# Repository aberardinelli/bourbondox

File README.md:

# bourbondox

`pcb/rev1` folder contains the KiCAD pcb files for v0.1 (received 2021-07-02)

`pcb/rev2` folder contains the KiCAD pcb files for v0.2 (received 2021-07-06)

`pcb/rev3` folder contains the KiCAD pcb files for v0.3 (received 2021-07-19)

`pcb/rev4` folder contains the KiCAD pcb files for v0.4 (received 2021-07-29)

`pcb/rev5` folder contains the KiCAD pcb files for v1.0 (received 2021-08-13)

`firmware` folder contains the qmk firmware files

`case/v1` folder contains the FreeCAD and dxf files for a stacked acrylic case that aligns with the v1.0 pcb (finished 2021-09-10)

There is also a json file (`keyboard-layout_rev1.0.json`) which could be used on keyboard-layout-editor.com

## Changelog and documentation of issues

### v0.1

* Only had one side printed. Diodes were mistakenly put on the front of the PCB in my schematic when they should be on the back.
* Soldered on reset button, promicro controller, and diodes.
* Tested each switch with tweezers. 
* All switches in columns 0, 1, 2, 3, and 4 worked as expected.
* All switches in columns 5 and 6 failed to register. Reset button failed to work.

### v0.2

* Had both sides printed this time. Completely redid the routing from scratch because I wasn't happy with the first version. Did all this and ordered the v0.2 prototypes before I had even received and tested v0.1.
* Soldered reset buttons, TRRS jacks, OLED screens, promicro controllers, diodes, and switches on both halves. Soldered resistors on right side only.
* Reset buttons still didn't work.  But... On each side, when plugged in alone (not connected to other half): All switches worked as expected. Both OLED screens worked as expected.
* When the sides are connected via TRRS cable, switches and OLED screens stopped working. This led me to believe there was a problem with the routing with the TRRS jacks. I ruled out a problem with the cable since I tried two different TRRS cables, both of which worked fine with two other split keyboards.
* Stagger on left hand felt extremely comfortable but right hand was unnatural.

### v0.3

* Changed the footprints on the PCB for the TRRS jacks and reset switches. Rerouted those components on the schematic.
* Reduced the stagger by a small bit on the left side. Reduced the stagger by a lot on the right side.
* Reset buttons work now, on both halves. 
* When it comes to testing the TRRS connection, there are multiple outcomes depending on configuration:
    * If right half has Elite-C and it is connected via USB-C cable to the computer, no switches register and OLEDs are blank.
    * If left half has ProMicro and it is connected via micro USB cable to the computer, no switches register, but the OLEDs each show the same garbled output (first few letters are clear and correct but the rest is nonsense).
    * If NOT connected via TRRS, but each half is connected via its respective USB cable directly to the computer, then OLED screens work as expected and all switches register as expected with tweezers.
* Stagger on left hand seems perfect; right hand might still need adjustments on pinky but seems perfect now for middle and ring fingers. 

### v0.4

* Changed the split communication to serial to allow OLED screens to use i2c. This required changing the routing and footprints in the schematics for the TRRS jacks.
* Very minor adjustments made to spacing of holes for OLED covers.
* Thumb cluster on right side was not great for my use case; rotated the keys on that side. 
* Increased the spacebar size on left side to 2u for more likely compatibility with keycap kits.

## v1.0 photos

*Initial build of v1.0 with cheap tenting provided by acrylic photo frames*

*v1.0 with better tenting provided by magnetic cell phone holders*

## v0.4 photo

*First fully functional build!*

## v0.3 photos

*Not plugged in*

*Halves are NOT connected, each half is connected to computer via its own cable. OLEDs, switches, and reset buttons work as expected*

*TRRS connecting the halves, connected to computer via USB-C cable plugged into Elite-C controller on right half of keyboard (controller power buttons light up, but no OLEDs and no switches register)*

*TRRS connecting the halves, connected to computer via micro USB cable plugged into ProMicro controller on left half of keyboard (controller power buttons light up, but no switches register; OLEDs light up but output is garbled)*

## v0.2 photo

*Everything's soldered, but it's not plugged in*

## v0.1 photos

*No soldering done yet, just placing switches and keycaps to verify fit.*

*Soldered diodes, promicro, and reset button to the front. Yes, I know the diodes are supposed to be on the back of the PCB. This is fixed for v0.2.*

*View of the soldering for the promicro on the back of the PCB.*

*Promicro is flashed and soldered. Ready for testing!*

# Acknowledgements

Thank you to ai03 and masterzen for your extensive keyboard pcb design tutorials posted online as resources for the community.

Thank you to the designers of the redox, lily58, and corne-cherry for sharing your work as open source. These were inspirational and helpful resources during my design of this keyboard.

Special thanks to the Keycraft Collective discord community, especially users astra and matthewdias, for their encouragement, feedback, input, and troubleshooting.

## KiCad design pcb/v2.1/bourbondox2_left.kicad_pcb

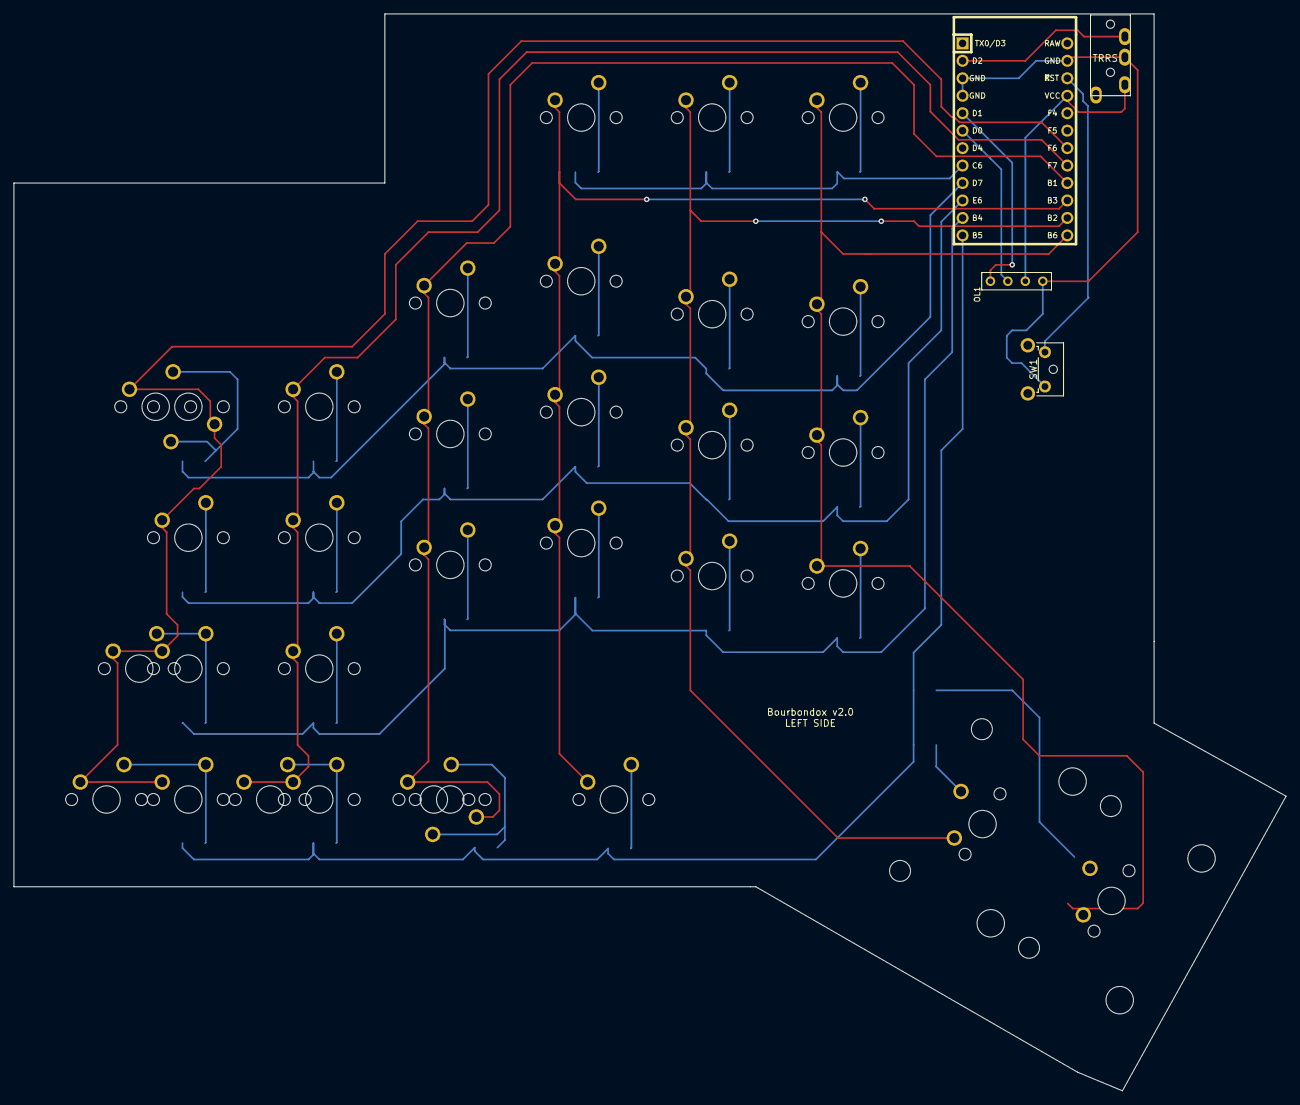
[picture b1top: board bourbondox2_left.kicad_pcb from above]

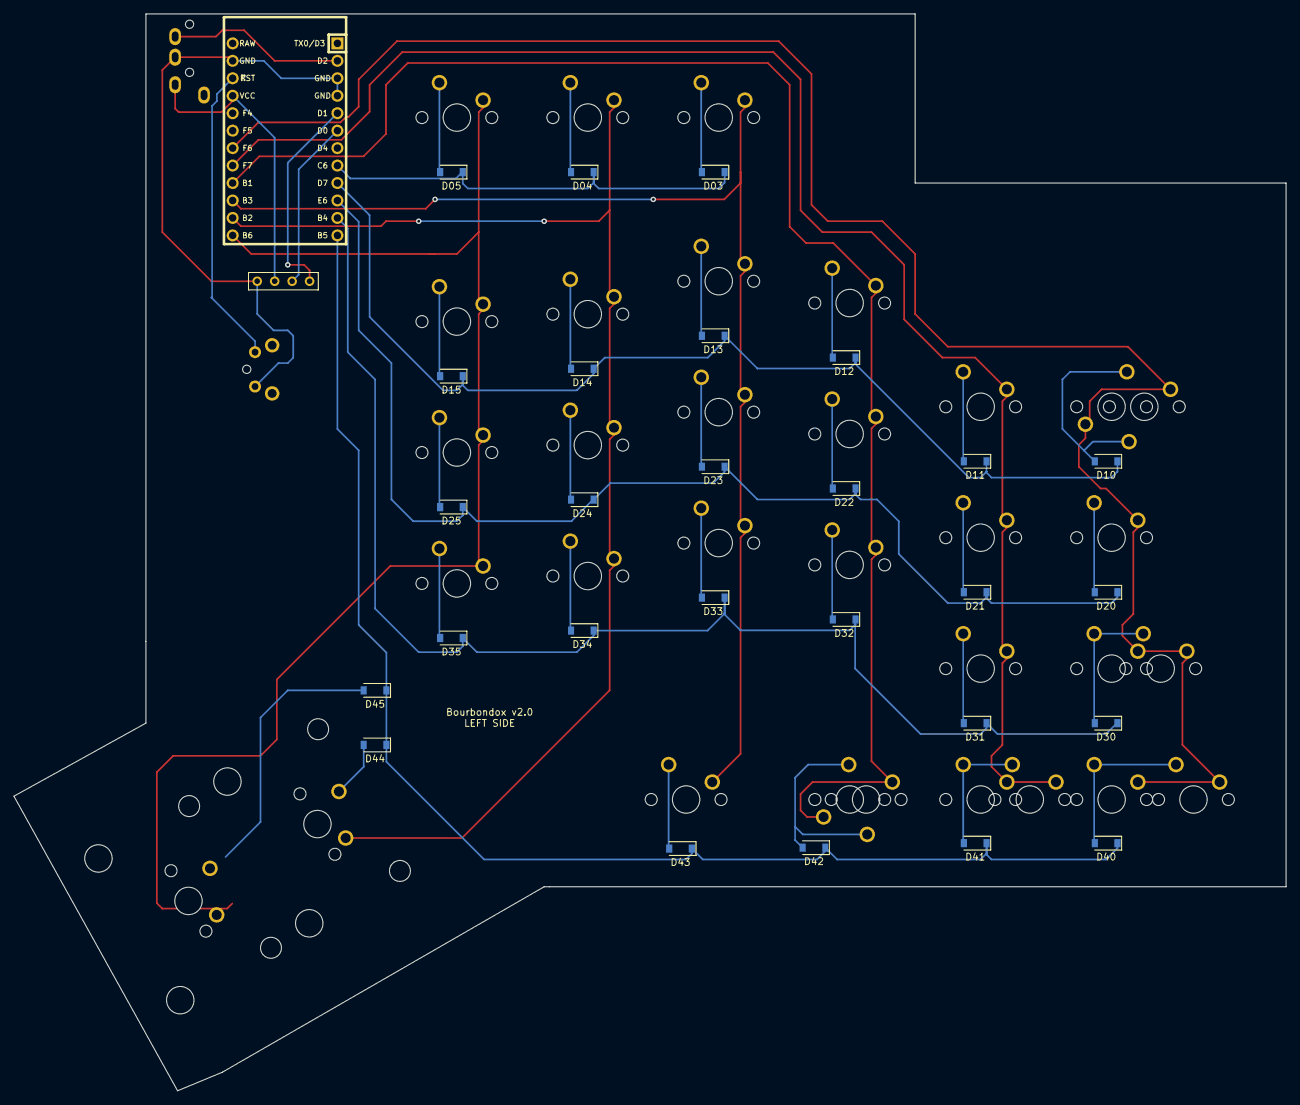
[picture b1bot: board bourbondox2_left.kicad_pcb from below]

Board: 2 copper layers, 185.1 x 156.7 mm, 63 parts (27 on the bottom side), 44 nets.

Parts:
D03, D04, D05, D10, D11, D12, D13, D14, D15, D20, D21, D22, D23, D24, D25, D30, D31, D32, D33, D34, D35, D40, D41, D42, D43, D44, D45: D_Small; D_SOD-123
J1: MJ-4PP-9; MJ-4PP-9_1side
MX03, MX04, MX05, MX10, MX11, MX12, MX13, MX14, MX15, MX20, MX21, MX22, MX23, MX24, MX25, MX30, MX31, MX32, MX33, MX34, MX35, MX40, MX41, MX42: MX-NoLED; MXOnly-1U-NoLED
MX10_2, MX43: MX-NoLED; MXOnly-1.5U-NoLED
MX30_2: MX-NoLED; MXOnly-1.75U-NoLED
MX40_2, MX41_2, MX42_2: MX-NoLED; MXOnly-1.25U-NoLED
MX44, MX45: MX-NoLED; MXOnly-2.25U-NoLED
OL1: OLED; OLED_4Pin
SW1: SW_Push; SW_Tactile_SPST_Angled_MJTP1117
U1: ProMicro; ArduinoProMicro

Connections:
DATA: J1.B, U1.2
GND: J1.C, OL1.4, SW1.2, U1.3, U1.4, U1.23
unnamed: D03.2, MX03.2
unnamed: D04.2, MX04.2
unnamed: D05.2, MX05.2
unnamed: D10.2, MX10.2, MX10_2.2
unnamed: D11.2, MX11.2
unnamed: D12.2, MX12.2
unnamed: D13.2, MX13.2
unnamed: D14.2, MX14.2
unnamed: D15.2, MX15.2
unnamed: D20.2, MX20.2
unnamed: D21.2, MX21.2
unnamed: D22.2, MX22.2
unnamed: D23.2, MX23.2
unnamed: D24.2, MX24.2
unnamed: D25.2, MX25.2
unnamed: D30.2, MX30.2, MX30_2.2
unnamed: D31.2, MX31.2
unnamed: D32.2, MX32.2
unnamed: D33.2, MX33.2
unnamed: D34.2, MX34.2
unnamed: D35.2, MX35.2
unnamed: D40.2, MX40.2, MX40_2.2
unnamed: D41.2, MX41.2, MX41_2.2
unnamed: D42.2, MX42.2, MX42_2.2
unnamed: D43.2, MX43.2
unnamed: D44.2, MX44.2
unnamed: D45.2, MX45.2
RESET: SW1.1, U1.22
SCL: OL1.2, U1.6
SDA: OL1.1, U1.5
VCC: J1.D, OL1.3, U1.21
col0: MX10.1, MX10_2.1, MX20.1, MX30.1, MX30_2.1, MX40.1, MX40_2.1, U1.18
col1: MX11.1, MX21.1, MX31.1, MX41.1, MX41_2.1, U1.17
col2: MX12.1, MX22.1, MX32.1, MX42.1, MX42_2.1, U1.16
col3: MX03.1, MX13.1, MX23.1, MX33.1, MX43.1, U1.15
col4: MX04.1, MX14.1, MX24.1, MX34.1, MX44.1, U1.14
col5: MX05.1, MX15.1, MX25.1, MX35.1, MX45.1, U1.13
row0: D03.1, D04.1, D05.1, U1.8
row1: D10.1, D11.1, D12.1, D13.1, D14.1, D15.1, U1.9
row2: D20.1, D21.1, D22.1, D23.1, D24.1, D25.1, U1.10
row3: D30.1, D31.1, D32.1, D33.1, D34.1, D35.1, U1.11
row4: D40.1, D41.1, D42.1, D43.1, D44.1, D45.1, U1.12

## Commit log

2021-07-05 Uploaded QMK firmware files and v0.1 pcb files
2021-07-05 Renamed folders for clarity; added photos
2021-07-11 Started v0.3; left side modifications done: slightly decreased pinky stagger, added holes for OLED cover, rerouted TRRS and reset button
2021-07-11 Started edits for right side for v0.3; added holes for OLED cover, fixed TRRS and reset switch footprints
2021-07-11 Fixed routing for right side for v0.3
2021-07-11 Finalized routing for right side of v0.3
2021-07-11 Generated gerber files for v0.3
2021-07-25 Updated README and added new pictures
2021-07-25 Minor changes to README
2021-07-25 Created folder for v0.4; modified TRRS jack in schematic to serial communication
2021-07-25 Fixed footprint for TRRS jack in right side and rerouted.
2021-07-25 Fixed footprint for TRRS jack in left side and rerouted.
2021-07-25 Updated silks for v0.4
2021-07-25 Added acknowledgements section
2021-07-25 Moved the OLED cover holes slightly for better fit
2021-07-25 Repositioned both thumb clusters; fixed positioning of z key on left side
2021-07-25 Added documentation about what was adjusted in v0.4
2021-07-25 Modified firmware for serial split communication
2021-08-01 Started final(?) revision, v1.0
2021-08-01 Modified right side: moved misc components under OLED cover, added keys in column 6
2021-09-10 Updated README, added latest firmware, case, and pcb files
2021-09-26 Updated firmware
2021-10-10 Reorganized folder structure
2021-10-10 Updated README to match new directory structure
2021-11-10 Generated files for v2 case printing
2022-04-13 v2.0 of pcb added
2022-07-28 Modifications to PCB made on laptop
2024-01-09 Cleaning files off Asus ZenBook
